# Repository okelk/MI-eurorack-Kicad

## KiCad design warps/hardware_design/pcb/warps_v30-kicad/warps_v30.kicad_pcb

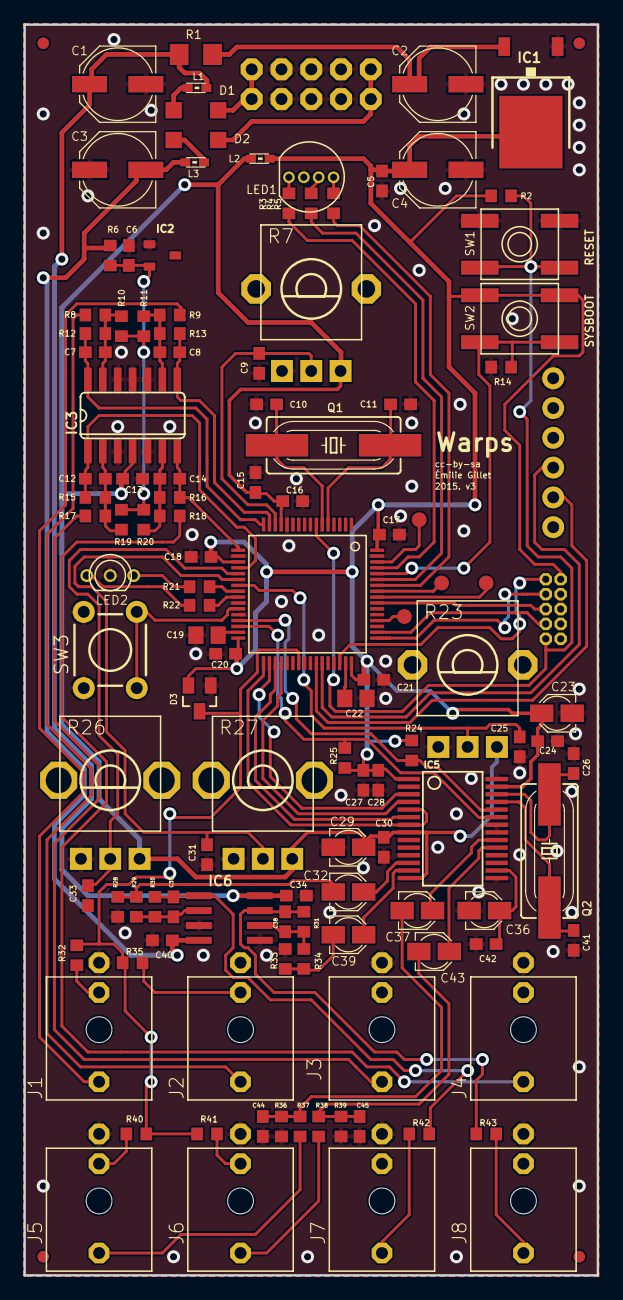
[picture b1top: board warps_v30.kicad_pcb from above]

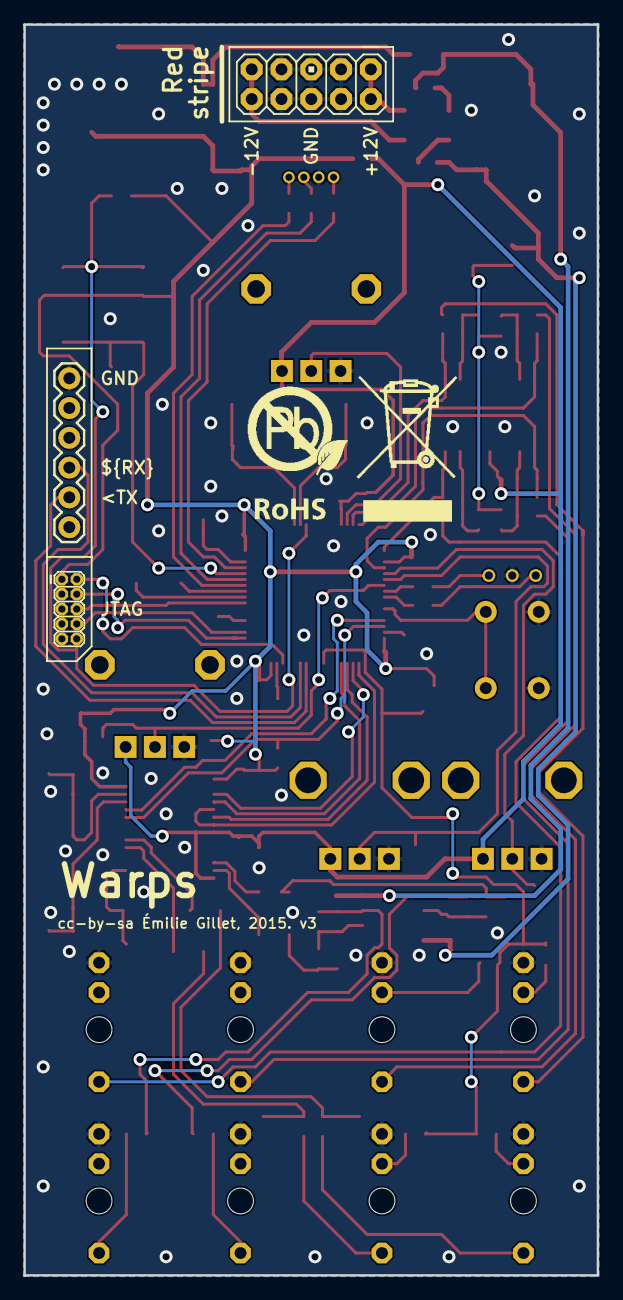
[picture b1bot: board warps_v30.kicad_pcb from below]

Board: 2 copper layers, 48.9 x 106.7 mm, 127 parts (4 on the bottom side), 84 nets.

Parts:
C1, C2, C3, C4: 47u; PANASONIC_D
C5, C6, C9, C13, C16, C17, C18, C20, C21, C24, C25, C28, C30, C31, C33, C34, C40, C42: 100n; C0603
C7, C8, C12, C14: 4.7n; C0603
C10, C11, C26, C35, C38, C41: 18p; C0603
C15, C27: 1u; C0603
C19, C22: 2.2u; C0805
C23, C29, C32, C36, C37, C39, C43: 10u; PANASONIC_A
C44, C45: 220p; C0603
D1, D2: 1N5819HW; SOD123
D3: BAT54S; SOT23
F1, F2, F3, F4: FIDUCIAL1X2; FIDUCIAL-1X2
IC1: LM1117-3.3; TO252
IC2: LM4040B10; DBZ_R-PDSO-G3
IC3: MCP6004; SO14
IC4: STM32F405RGT6; TQFP-10X10-64
IC5: WM8731; SSOP28
IC6: TL072; SO08
J1, J2, J3, J4, J5, J6, J7, J8: PJ301_THONKICONN6; WQP_PJ_301M6
JP1: M05X2MINIJTAG; 2X5-1.27
JP2: 1X06
JP3: M05X2PTH; AVR_ICSP
L1, L2, L3: 0603
LED1: WP154A4SUREQBFZG; LED-TRICOLOR-THROUGHHOLE
LED2: WP115VEGW; LED-BICOLOR-THROUGHHOLE
Q1: 8MHz; HC49UP
Q2: 12.288MHz; HC49UP
R1: 4.7; R1206
R2, R14: 10k; R0603
R3, R4, R5: 100; R0603
R6: 4.7k; R0603
R7, R23: 10kB; ALPS_POT_VERTICAL_PS
R8, R9, R17, R18: 100k; R0603
R10, R11: 120k; R0603
R12, R13, R37, R38: 36k; R0603
R15, R16: 33k; R0603
R19, R20, R32, R35: 200k; R0603
R21, R22: 180; R0603
R24, R25: 2.2k; R0603
R26, R27: 10kB; ALPS_POT_VERTICAL
R28, R30, R31, R33: 47k; R0603
R29, R34, R36, R39: 6.8k; R0603
R40, R41: DNP; R0603
R42, R43: 1.0k; R0603
SW1, SW2: EVQ-Q2
SW3: TACTILE-PTH
TP1, TP2, TP3, TP4: TEST-POINT3X5; PAD.03X.05
U$2: ROHS_BIG

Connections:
+3V3: C4.+, C5.1, C17.1, C18.1, C20.1, C21.1, C23.+, C24.1, C27.1, C28.1, D3.2, IC1.3, IC4.19, IC4.32, IC4.48, IC4.64, IC5.1, IC5.27, JP1.1, L2.1, R2.2, R24.2, R25.2, SW2.B, SW2.B'
+3V3_A: C13.1, C15.1, C16.1, C29.+, C30.1, IC3.4, IC4.13, IC5.8, IC5.14, L2.2, R7.P$1, R23.P$1, R26.P$1, R27.P$1
ALGORITHM_CV: C12.2, IC3.1, IC4.20, R15.1
ALGORITHM_POT: C9.1, IC4.14, R7.P$2
AREF_-10: C6.1, IC2.2, R6.2, R10.2, R11.2, R19.2, R20.2
AUX_OUT: C39.+, IC5.13
BOOT_FLASH: IC4.60, R14.2, SW2.A, SW2.A'
GND: C1.-, C2.-, C3.+, C4.-, C5.2, C6.2, C9.2, C10.1, C11.1, C13.2, C15.2, C16.2, C17.2, C18.2, C19.2, C20.2, C21.2, C22.2, C23.-, C24.2, C25.2, C26.1, C27.2, C28.2, C29.-, C30.2, C31.2, C33.2, C34.2, C36.-, C40.1, C41.1, C42.2, C44.2, C45.2, D3.1, IC1.1, IC2.1, IC3.3, IC3.5, IC3.10, IC3.11, IC3.12, IC4.12, IC4.18, IC4.26, IC4.28, IC4.63, IC5.11, IC5.15, IC5.21, IC5.22, IC5.28, IC6.3, IC6.5, J1.P1, J2.P1, J3.P1, J4.P1, J5.P1, J6.P1, J7.P1, J8.P1, JP1.3, JP1.5, JP1.9, JP2.1, JP3.3, JP3.4, JP3.5, JP3.6, JP3.7, JP3.8, LED1.GND, LED2.2, R7.P$3, R14.1, R23.P$3, R26.P$3, R27.P$3, R28.1, R33.1, R36.1, R39.1, SW1.A, SW1.A', SW3.1, SW3.2
I2C_SCL: IC4.29, IC5.24, R24.1
I2C_SDA: IC4.30, IC5.23, R25.1
I2S_LRCK: IC4.33, IC5.5, IC5.7
I2S_SCK: IC4.34, IC5.3
I2S_SIN: IC4.35, IC5.6
I2S_SOUT: IC4.36, IC5.4
IN_1: C37.+, IC5.20
IN_2: C43.+, IC5.19
JTCK: IC4.49, JP1.4
JTDI: IC4.50, JP1.8
JTDO: IC4.55, JP1.6
JTMS: IC4.46, JP1.2
LED_B: IC4.59, R4.1
LED_CARRIER_G: IC4.25, R22.1
LED_CARRIER_R: IC4.24, R21.1
LED_G: IC4.58, R5.1
LED_R: IC4.61, R3.1
LEVEL_1_CV: C8.2, IC3.8, IC4.15, R13.1
LEVEL_1_POT: C33.1, IC4.21, R26.P$2
LEVEL_2_CV: C7.2, IC3.14, IC4.16, R12.1
LEVEL_2_POT: C31.1, IC4.22, R27.P$2
MOD_OUT: C32.+, IC5.12
unnamed: J1.P3, R9.2
unnamed: C8.1, IC3.9, R9.1, R11.1, R13.2
unnamed: LED2.3, R21.2
unnamed: J2.P3, R8.2
unnamed: C7.1, IC3.13, R8.1, R10.1, R12.2
unnamed: J4.P3, R18.2
unnamed: C11.2, IC4.5, Q1.2
unnamed: C10.2, IC4.6, Q1.1
unnamed: J1.P2, R32.2
unnamed: J3.P3, R17.2
unnamed: C12.1, IC3.2, R15.2, R17.1, R19.1
unnamed: J2.P2, R35.2
unnamed: C22.1, IC4.47
unnamed: LED2.1, R22.2
unnamed: C14.1, IC3.6, R16.2, R18.1, R20.1
unnamed: C2.+, IC1.2, R1.1
unnamed: C36.+, C42.1, IC5.16
unnamed: C37.-, C44.1, R36.2, R37.1
unnamed: C19.1, IC4.31
unnamed: J6.P3, R38.2
unnamed: J5.P3, R37.2
unnamed: C43.-, C45.1, R38.1, R39.2
unnamed: C39.-, R33.2, R34.2
unnamed: IC4.56, TP3.P$1
unnamed: C38.1, IC6.6, R31.2, R34.1
unnamed: IC4.57, TP2.P$1
unnamed: IC4.52, TP4.P$1
unnamed: C38.2, IC6.7, R31.1, R43.2
unnamed: J8.P3, R43.1
unnamed: IC4.62, TP1.P$1
unnamed: C32.-, R28.2, R29.2
unnamed: C35.1, IC6.2, R29.1, R30.2
unnamed: C35.2, IC6.1, R30.1, R42.2
unnamed: J7.P3, R42.1
unnamed: LED1.RED, R3.2
unnamed: LED1.BLU, R4.2
unnamed: LED1.GRN, R5.2
unnamed: J6.P2, R41.1
unnamed: J5.P2, R40.1
unnamed: C41.2, IC5.25, Q2.2
unnamed: C26.2, IC5.26, Q2.1
unnamed: D1.C, L1.2
unnamed: D2.A, L3.2
unnamed: D1.A, JP3.1, JP3.2
unnamed: D2.C, JP3.9, JP3.10
NORMALIZATION_PROBE: D3.3, IC4.39, R32.1, R35.1, R40.2, R41.2
PARAMETER_CV: C14.2, IC3.7, IC4.17, R16.1
PARAMETER_POT: C25.1, IC4.23, R23.P$2
RESET: IC4.7, JP1.10, R2.1, SW1.B, SW1.B'
RX: IC4.43, JP2.4
SW_CARRIER: IC4.27, SW3.3, SW3.4
TX: IC4.42, JP2.5
VCC: C1.+, C34.1, IC6.8, L1.1, R1.2
VEE: C3.-, C40.2, IC6.4, L3.1, R6.1

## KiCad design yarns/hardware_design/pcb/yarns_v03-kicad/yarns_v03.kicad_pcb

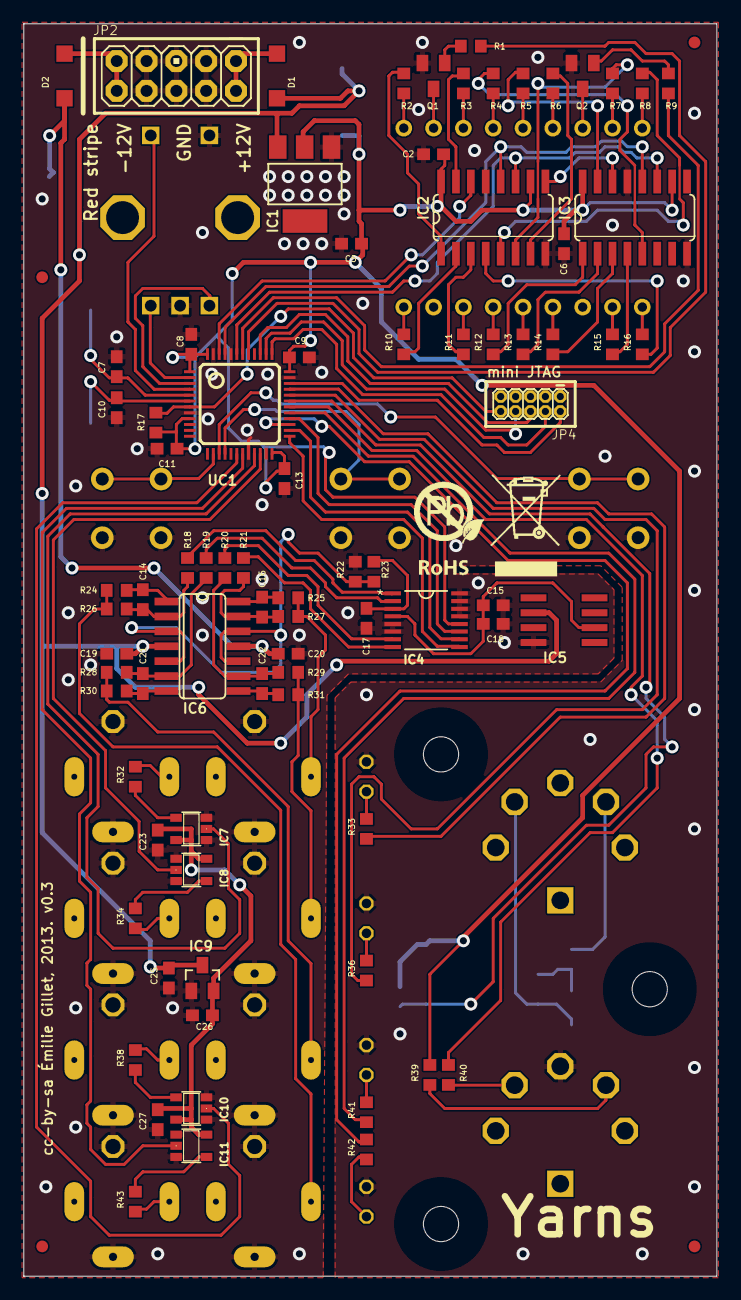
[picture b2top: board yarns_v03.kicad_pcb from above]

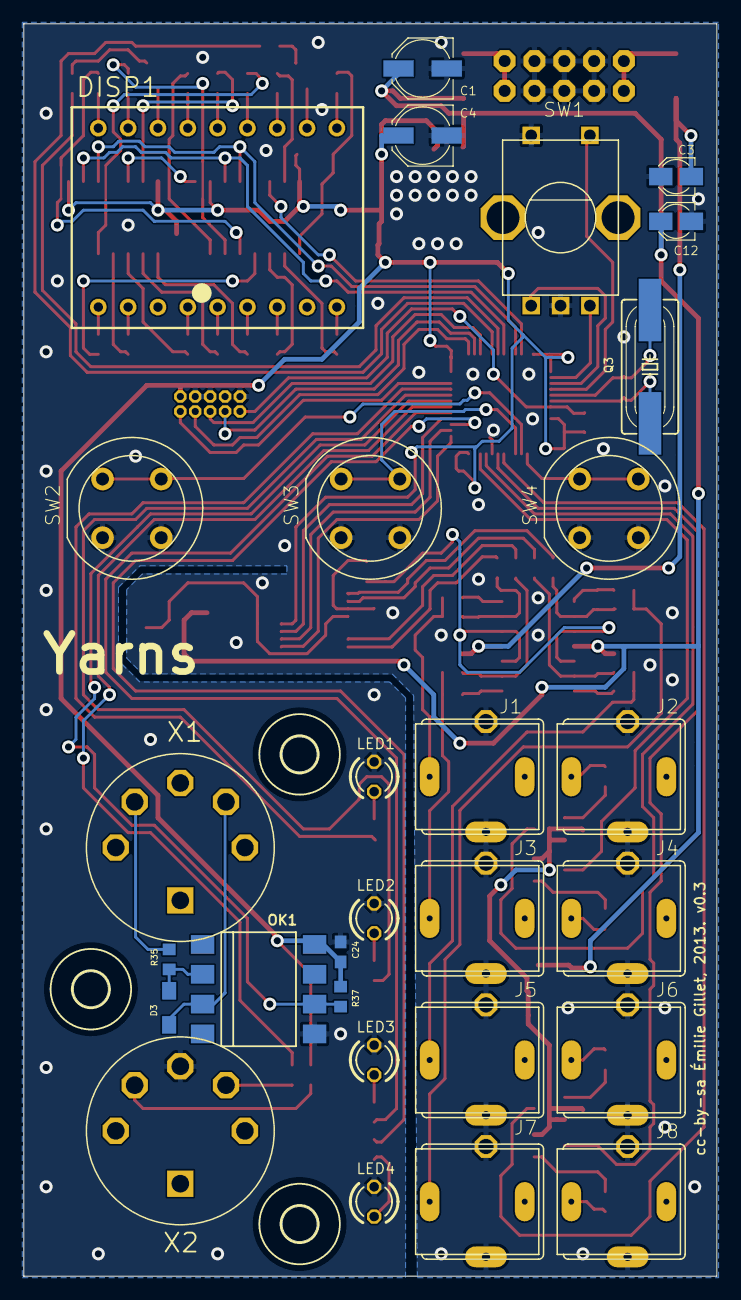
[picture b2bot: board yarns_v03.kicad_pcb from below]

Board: 2 copper layers, 59.0 x 106.7 mm, 118 parts (32 on the bottom side), 107 nets.

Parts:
C1, C4: 22u; PANASONIC_C
C2, C5, C6, C8, C9, C11, C13, C18, C19, C20, C23, C24, C27: 100n; C0603
C3, C12: 10u; PANASONIC_A
C7, C10, C14, C16, C21, C22: 18p; C0603
C15: 3.3u; C0603
C17: 220n; C0603
C25, C26: 1u; C0603
D1, D2: 1N5819HW; SOD123
D3: 1N4148; SOD323-W
DISP1: KINGBRIGHT-PDC54-11; PDC54
F1, F3, F5, F6: FIDUCIAL1X2; FIDUCIAL-1X2
IC1: LM1117-3.3; SOT223
IC2, IC3: 74HC595D; SO16
IC4: DAC8564; SOP65P640X110-16N
IC5: REF02D; SO08
IC6: OPA4171; SO14
IC7, IC8, IC10, IC11: 74AHCT1G125DBV; SOT23-5
IC9: MCP1703CB; SOT23
J1, J2, J3, J4, J5, J6, J7, J8: PJ301WQP; WQP_PJ_301BM
JP2: M05X2PTH; AVR_ICSP
JP4: 2X5-1.27
LED1, LED2, LED3, LED4: LED3MM
OK1: 6N137SMT; DIL8-SMD
Q1, Q2: MMBT3904; SOT23-BEC
Q3: 8MHz; HC49UP
R1, R9, R24, R25, R30, R31, R32, R34, R38, R43: 1.0k; R0603
R2, R3, R4, R5, R6, R7, R8, R10, R11, R12, R13, R14, R15, R16, R33, R36, R41, R42: 100; R0603
R17, R37: 10k; R0603
R18, R19, R20, R21, R22, R23: 47k; R0603
R26, R27, R28, R29: 240k; R0603
R35: 220; R0603
R39, R40: 51; R0603
SW1: EC12E_SW; ALPS_EC12E_SW
SW2: D6R40F2LFS; D6R
SW3, SW4: D6R
U$2, U$3, U$4: 3,0
U$5: ROHS
UC1: STM32F103CBT6; LQFP48
X1, X2: CUI-SD-50BV; SD-50BV

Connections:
+3V3: C2.1, C4.+, C5.1, C6.1, C8.1, C9.1, C11.1, C13.1, C24.1, IC1.2, IC2.10, IC2.16, IC3.10, IC3.16, IC4.12, JP4.1, OK1.8, R17.2, R37.2, R39.2, UC1.1, UC1.9, UC1.24, UC1.36, UC1.48
+5V: C15.1, C18.1, IC4.4, IC5.6
+5VD: C23.1, C26.1, C27.1, IC7.5, IC8.5, IC9.2, IC10.5, IC11.5
AOUT: J2.TIP, R32.1
CH_A: IC4.1, R18.2
CH_B: IC4.2, R19.2
CH_C: IC4.7, R20.2
CH_D: IC4.8, R21.2
DAC_MOSI: IC4.11, UC1.28
DAC_SCK: IC4.10, UC1.26
DAC_SS: IC4.9, UC1.25
DISP_CHAR0: R9.1, UC1.42
DISP_CHAR1: R1.1, UC1.41
DISP_EN: IC2.12, IC3.12, UC1.45
DISP_SCK: IC2.11, IC3.11, UC1.43
DISP_SER: IC2.14, UC1.46
ENC_A: SW1.B, UC1.2
ENC_B: SW1.A, UC1.3
ENC_CLICK: SW1.E, UC1.4
GATE_A: IC7.2, UC1.21
GATE_B: IC8.2, UC1.22
GATE_C: IC10.2, UC1.18
GATE_D: IC11.2, UC1.19
GND: C1.-, C2.2, C3.+, C4.-, C5.2, C6.2, C7.1, C8.2, C9.2, C10.1, C11.2, C12.-, C13.2, C15.2, C17.2, C18.2, C19.2, C20.1, C23.2, C24.2, C25.2, C26.2, C27.2, IC1.1, IC2.8, IC2.13, IC3.8, IC3.13, IC4.5, IC4.6, IC4.13, IC4.14, IC4.15, IC4.16, IC5.4, IC7.1, IC7.3, IC8.1, IC8.3, IC9.1, IC10.1, IC10.3, IC11.1, IC11.3, J1.GND, J1.GND2, J2.GND, J2.GND2, J3.GND, J3.GND2, J4.GND, J4.GND2, J5.GND, J5.GND2, J6.GND, J6.GND2, J7.GND, J7.GND2, J8.GND, J8.GND2, JP2.3, JP2.4, JP2.5, JP2.6, JP2.7, JP2.8, JP4.3, JP4.5, JP4.9, LED1.K, LED2.K, LED3.K, LED4.K, OK1.5, Q1.E, Q2.E, R22.1, SW1.C, SW1.D, SW2.B1, SW2.B2, SW3.B1, SW3.B2, SW4.B1, SW4.B2, UC1.8, UC1.20, UC1.23, UC1.35, UC1.44, UC1.47, X2.2
JTCK: JP4.4, UC1.37
JTDI: JP4.8, UC1.38
JTDO: JP4.6, UC1.39
JTMS: JP4.2, UC1.34
LED_1: R33.1, UC1.33
LED_2: R36.1, UC1.32
LED_3: R41.1, UC1.29
LED_4: R42.1, UC1.27
MIDI_RX: OK1.6, R37.1, UC1.31
MIDI_TX: R40.2, UC1.30
unnamed: DISP1.16, Q2.C
unnamed: C22.1, IC6.9, R20.1, R29.2
unnamed: DISP1.11, Q1.C
unnamed: C7.2, Q3.2, UC1.5
unnamed: C10.2, Q3.1, UC1.6
unnamed: Q2.B, R9.2
unnamed: Q1.B, R1.2
unnamed: D3.C, OK1.2, R35.1
unnamed: R35.2, X1.4
unnamed: R40.1, X2.5
unnamed: DISP1.17, R7.2
unnamed: D3.A, OK1.3, X1.5
unnamed: R39.1, X2.4
unnamed: IC7.4, R32.2
unnamed: DISP1.12, R3.2
unnamed: DISP1.10, R2.2
unnamed: DISP1.9, R10.2
unnamed: DISP1.7, R11.2
unnamed: DISP1.1, R16.2
unnamed: DISP1.18, R8.2
unnamed: DISP1.15, R6.2
unnamed: DISP1.14, R5.2
unnamed: DISP1.6, R12.2
unnamed: DISP1.5, R13.2
unnamed: DISP1.4, R14.2
unnamed: DISP1.2, R15.2
unnamed: DISP1.13, R4.2
unnamed: IC8.4, R34.2
unnamed: IC2.7, R6.1
unnamed: IC2.9, IC3.14
unnamed: IC2.15, R3.1
unnamed: IC2.1, R2.1
unnamed: IC2.2, R10.1
unnamed: IC2.3, R11.1
unnamed: IC2.4, R16.1
unnamed: IC2.5, R8.1
unnamed: IC2.6, R7.1
unnamed: IC3.15, R5.1
unnamed: IC3.1, R12.1
unnamed: IC3.2, R13.1
unnamed: IC3.3, R14.1
unnamed: IC3.4, R15.1
unnamed: IC3.5, R4.1
unnamed: IC10.4, R38.2
unnamed: IC11.4, R43.2
unnamed: C14.2, IC6.1, R24.2
unnamed: J6.TIP, R38.1
unnamed: J8.TIP, R43.1
unnamed: C21.2, IC6.7, R30.2
unnamed: C22.2, IC6.8, R31.2
unnamed: C16.2, IC6.14, R25.2
unnamed: J7.TIP, R24.1, R26.1
unnamed: LED1.A, R33.2
unnamed: J3.TIP, R29.1, R31.1
unnamed: D1.A, JP2.1, JP2.2
unnamed: J4.TIP, R34.1
unnamed: J1.TIP, R25.1, R27.1
unnamed: C16.1, IC6.13, R21.1, R27.2
unnamed: C21.1, IC6.6, R19.1, R28.2
unnamed: C14.1, IC6.2, R18.1, R26.2
unnamed: J5.TIP, R28.1, R30.1
unnamed: D2.C, JP2.9, JP2.10
unnamed: LED2.A, R36.2
unnamed: LED3.A, R41.2
unnamed: LED4.A, R42.2
RESET: JP4.10, R17.1, UC1.7
SWITCH_0: SW2.A1, SW2.A2, UC1.15
SWITCH_1: SW3.A1, SW3.A2, UC1.16
SWITCH_2: SW4.A1, SW4.A2, UC1.14
VCC: C1.+, C12.+, C19.1, C25.1, D1.C, IC1.3, IC5.2, IC6.4, IC9.3
VEE: C3.-, C20.2, D2.A, IC6.11
VREF: C17.1, IC4.3, R23.2
VREF/2: IC6.3, IC6.5, IC6.10, IC6.12, R22.2, R23.1

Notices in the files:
warps/hardware_design/pcb/warps_v30-kicad/warps_v30.kicad_pcb:
cc-by-sa
cc-by-sa Émilie Gillet, 2015. v3
yarns/hardware_design/pcb/yarns_v03-kicad/yarns_v03.kicad_pcb:
cc-by-sa Émilie Gillet, 2013. v0.3
